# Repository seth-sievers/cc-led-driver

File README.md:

# cc-led-driver
A "cc" buck converter for dimming LED strips

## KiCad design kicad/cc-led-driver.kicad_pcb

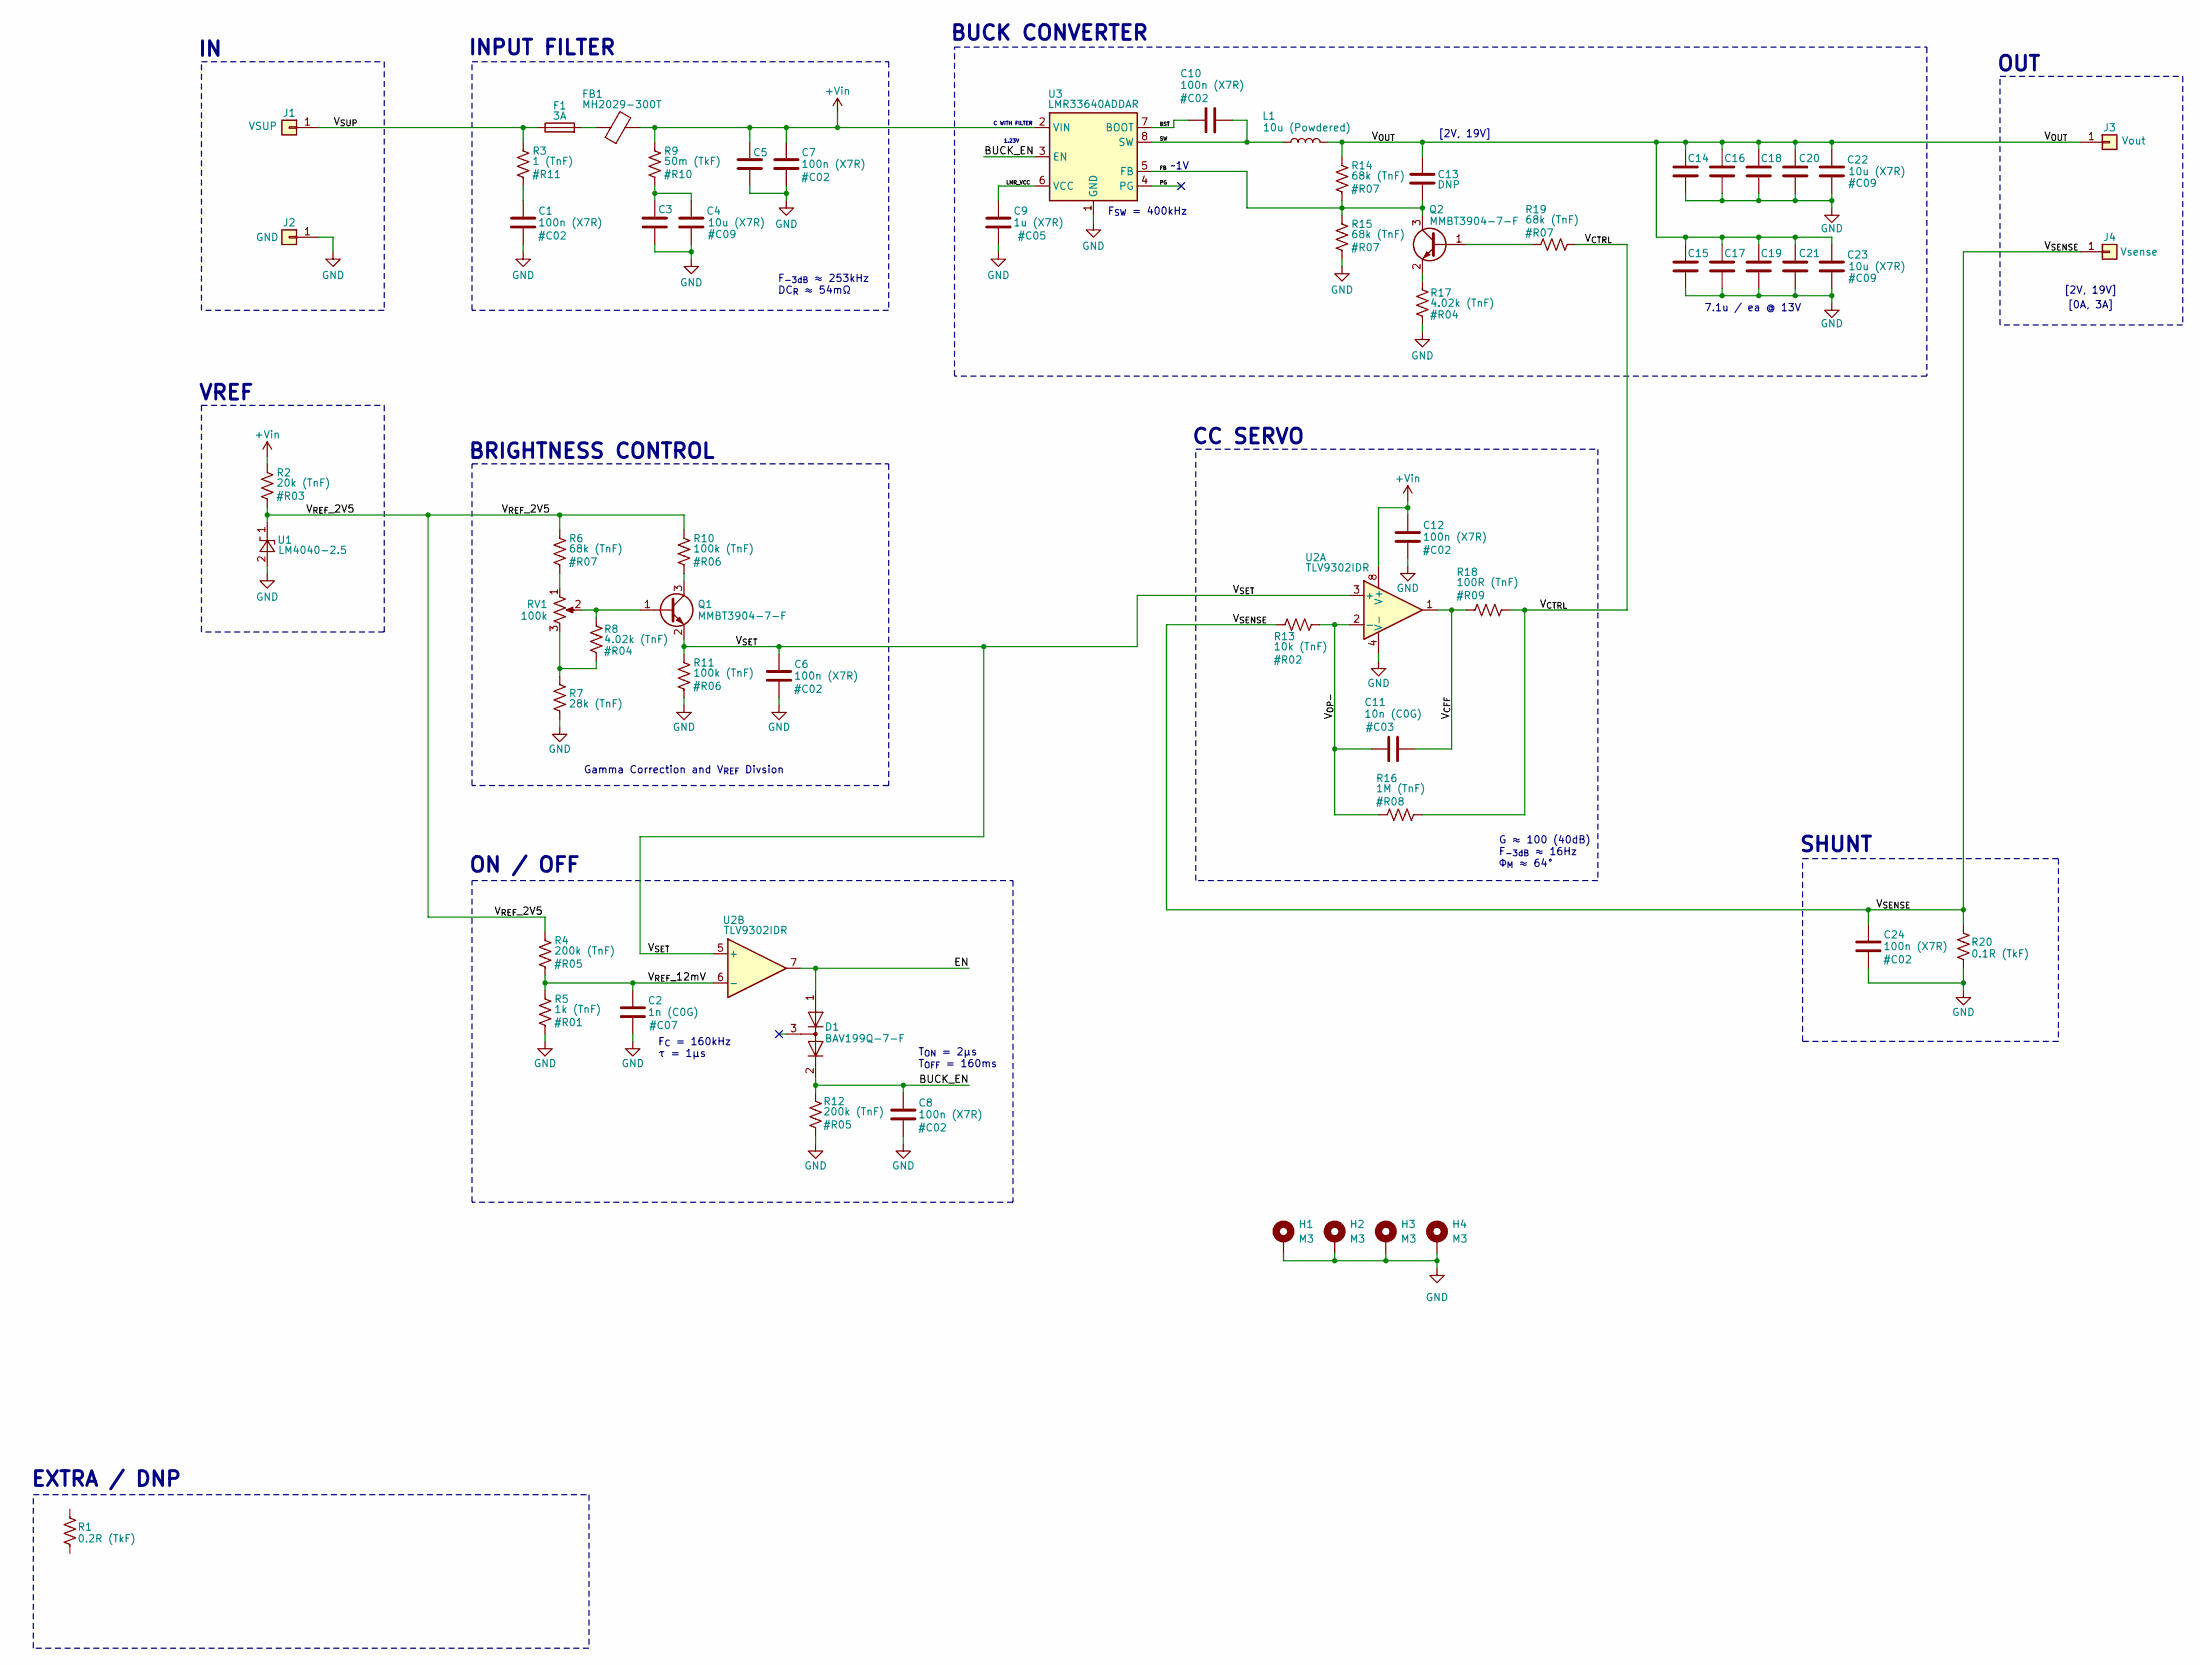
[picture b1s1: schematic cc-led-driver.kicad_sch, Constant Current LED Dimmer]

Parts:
C1, C5, C6, C7, C8, C10, C12, C24: 100n (X7R); C_0603_1608Metric
C2: 1n (C0G); C_0603_1608Metric
C3, C4, C14, C15, C16, C17, C18, C19, C20, C21, C22, C23: 10u (X7R); C_1210_3225Metric
C9: 1u (X7R); C_0603_1608Metric
C11: 10n (C0G); C_0603_1608Metric
C13: DNP; C_0603_1608Metric
D1: BAV199Q-7-F; SOT-23
F1: 3A; Fuse_1206_3216Metric
FB1: MH2029-300T; L_0805_2012Metric
H1, H2, H3, H4: M3; MountingHole_2.2mm_M2_DIN965_Pad
J1: VSUP; 20AWG
J2: GND; 20AWG
J3: Vout; 20AWG
J4: Vsense; 20AWG
L1: 10u (Powdered); L_Vishay_IHLP-4040
Q1, Q2: MMBT3904-7-F; SOT-23
R1: 0.2R (TkF); R_1206_3216Metric
R2: 20k (TnF); R_0603_1608Metric
R3: 1 (TnF); R_0603_1608Metric
R4, R12: 200k (TnF); R_0603_1608Metric
R5: 1k (TnF); R_0603_1608Metric
R6, R14, R15, R19: 68k (TnF); R_0603_1608Metric
R7: 28k (TnF); R_0603_1608Metric
R8, R17: 4.02k (TnF); R_0603_1608Metric
R9: 50m (TkF); R_0603_1608Metric
R10, R11: 100k (TnF); R_0603_1608Metric
R13: 10k (TnF); R_0603_1608Metric
R16: 1M (TnF); R_0603_1608Metric
R18: 100R (TnF); R_0603_1608Metric
R20: 0.1R (TkF); R_1206_3216Metric
RV1: 100k; Potentiometer_Bourns_PTV09A-1_Single_Vertical
U1: LM4040-2.5; SOT-23
U2: TLV9302IDR; SOIC-8_3.9x4.9mm_P1.27mm
U3: LMR33640ADDAR; Texas_HSOP-8-1EP_3.9x4.9mm_P1.27mm_ThermalVias

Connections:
+Vin: C5.1, C7.1, C12.1, FB1.2, R2.1, R9.1, U2.8 (V+), U3.2 (VIN)
/BST: C10.1, U3.7 (BOOT)
/BUCK_EN: C8.1, D1.2 (A), R12.1, U3.3 (EN)
/EN: D1.1 (K), U2.7
/FB: C13.2, Q2.3 (C), R14.2, R15.1, U3.5 (FB)
/LMR_VCC: C9.1, U3.6 (VCC)
/PG: U3.4 (PG)
/SW: C10.2, L1.1, U3.8 (SW)
/V_{CFF}: C11.2, R18.1, U2.1
/V_{CTRL}: R16.2, R18.2, R19.2
/V_{OP-}: C11.1, R13.2, R16.1, U2.2 (-)
/V_{OUT}: C13.1, C14.1, C15.1, C16.1, C17.1, C18.1, C19.1, C20.1, C21.1, C22.1, C23.1, J3.1, L1.2, R14.1
/V_{REF}_2V5: R2.2, R4.1, R6.1, R10.1, U1.1 (K)
/V_{REF}_12mV: C2.1, R4.2, R5.1, U2.6 (-)
/V_{SENSE}: C24.1, J4.1, R13.1, R20.1
/V_{SET}: C6.1, Q1.2 (E), R11.1, U2.3 (+), U2.5 (+)
/V_{SUP}: F1.1, J1.1, R3.1
GND: C1.2, C2.2, C3.2, C4.2, C5.2, C6.2, C7.2, C8.2, C9.2, C12.2, C14.2, C15.2, C16.2, C17.2, C18.2, C19.2, C20.2, C21.2, C22.2, C23.2, C24.2, H1.1, H2.1, H3.1, H4.1, J2.1, R5.2, R7.2, R11.2, R12.2, R15.2, R17.2, R20.2, U1.2 (A), U2.4 (V-), U3.1 (GND), U3.9 (GND)
unnamed: C1.1, R3.2
unnamed: C3.1, C4.1, R9.2
unnamed: F1.2, FB1.1
unnamed: Q1.1 (B), R8.1, RV1.2
unnamed: Q1.3 (C), R10.2
unnamed: Q2.1 (B), R19.1
unnamed: Q2.2 (E), R17.1
unnamed: R6.2, RV1.1
unnamed: R7.1, R8.2, RV1.3

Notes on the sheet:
C WITH FILTER
G ≈ 100 (40dB) F_{-3dB} ≈ 16Hz Φ_{M} ≈ 64°
BUCK CONVERTER
OUT
1.23V
INPUT FILTER
BRIGHTNESS CONTROL
EXTRA / DNP
CC SERVO
[2V, 19V]
[0A, 3A]
ON / OFF
F_{-3dB} ≈ 253kHz DC_{R} ≈ 54mΩ
T_{ON} = 2μs T_{OFF} = 160ms
SHUNT
Gamma Correction and V_{REF} Divsion
VREF
F_{C} = 160kHz τ = 1μs
~1V
F_{SW} = 400kHz
7.1u / ea @ 13V

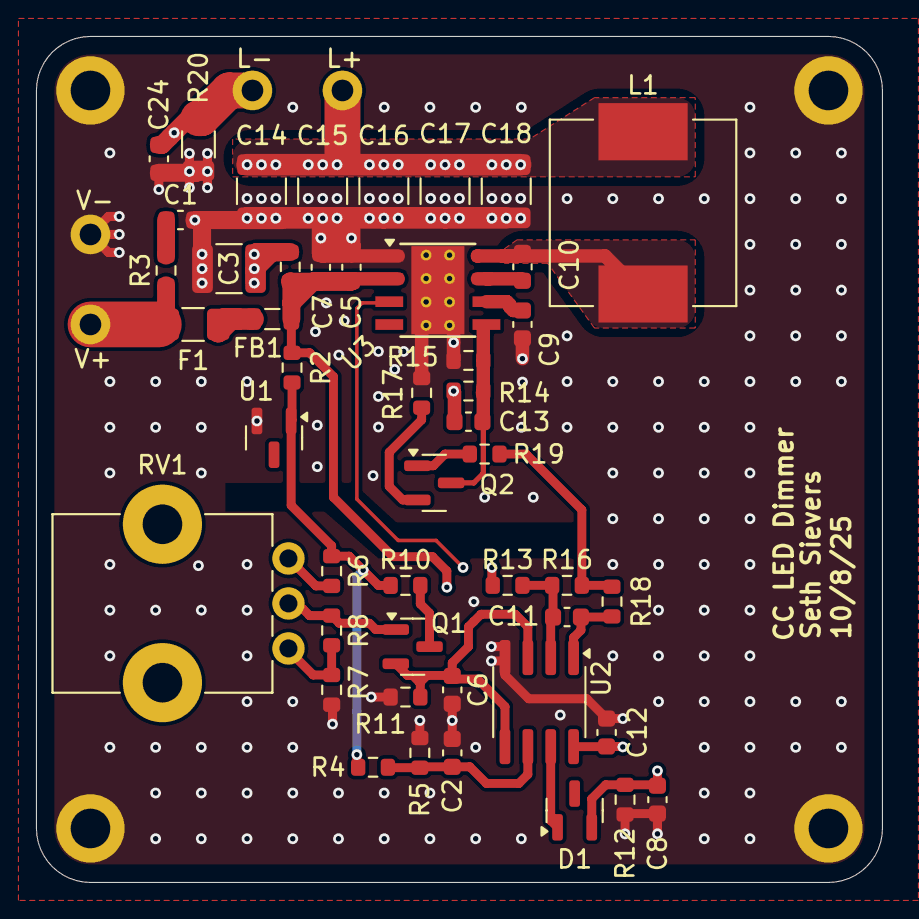
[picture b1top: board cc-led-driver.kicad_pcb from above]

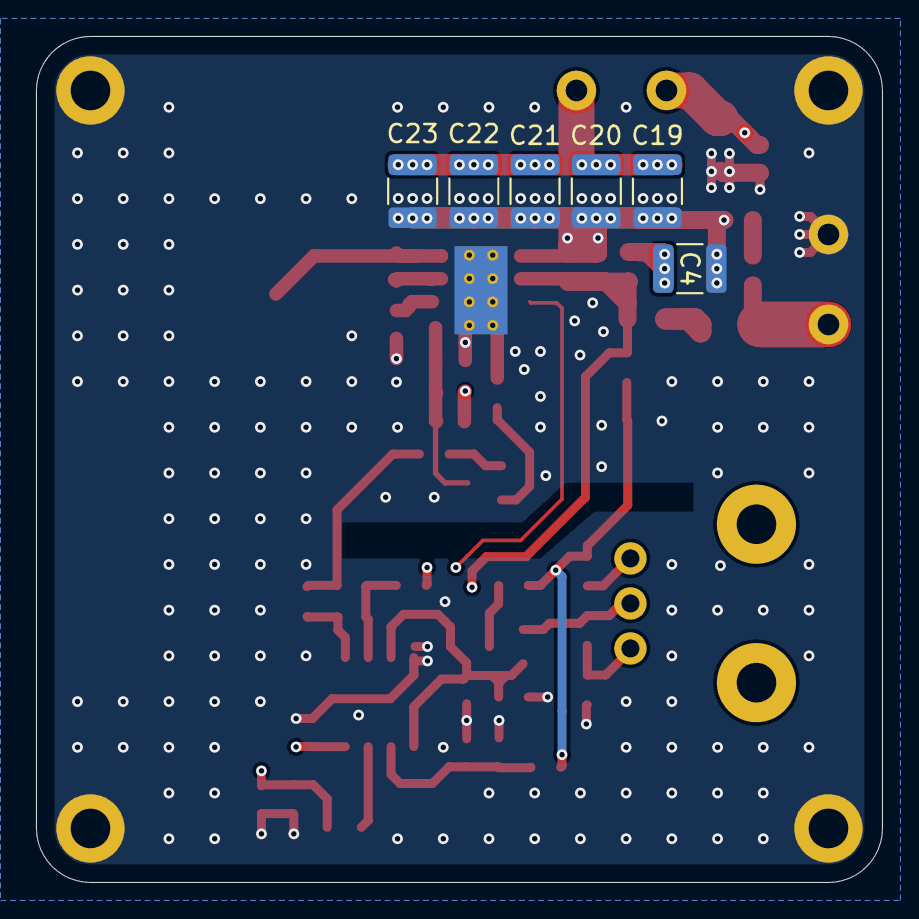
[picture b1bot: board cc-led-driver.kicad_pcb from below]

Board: 4 copper layers, 47.0 x 47.0 mm, 61 parts (6 on the bottom side), 26 nets.

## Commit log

2025-09-14 file sync
2025-09-15 gamma correction simulated
2025-09-22 progress on schematic
2025-09-25 sync
2025-10-10 completed schematic and ordered gerbers
2025-10-22 exported BOM
2025-10-31 update files
